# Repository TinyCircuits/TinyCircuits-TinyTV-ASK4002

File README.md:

# TinyCircuits TinyTV
# ASK4002

The design files are located under design_files/ for the TinyTV Remote, other design files can be found under the individual components' name on our GitHub. This Repo contains any files or documentation specific to the TinyTV.

Format is in Cadsoft Eagle format - Eagle version 6.2 was used for the original design.

For more infomation on this, check out the product page at TinyCircuits.com

# License:

Design by TinyCircuits.
All design files are released under the Creative Commons Attribution Share-Alike 3.0 License, see the following link for details: http://creativecommons.org/licenses/by-sa/3.0

All text above must be included in any redistribution or derived design

This project uses designs and concepts developed as part of the Arduino project and the LilyPad project.  The TinyCircuits design files themselves (schematics, PCB and libraries) are not directly derived from these works' design files and have been created new, however the concepts and basic architecture behind the TinyDuino and TinyLily products are derived and we thank the hard work of the organizations below for their contributions to open-source hardware:
  
Original Arduino Uno Design by Team Arduino

LilyPad Arduino Design by Leah Buechley and Sparkfun Electronics

Please support the open-source hardware community

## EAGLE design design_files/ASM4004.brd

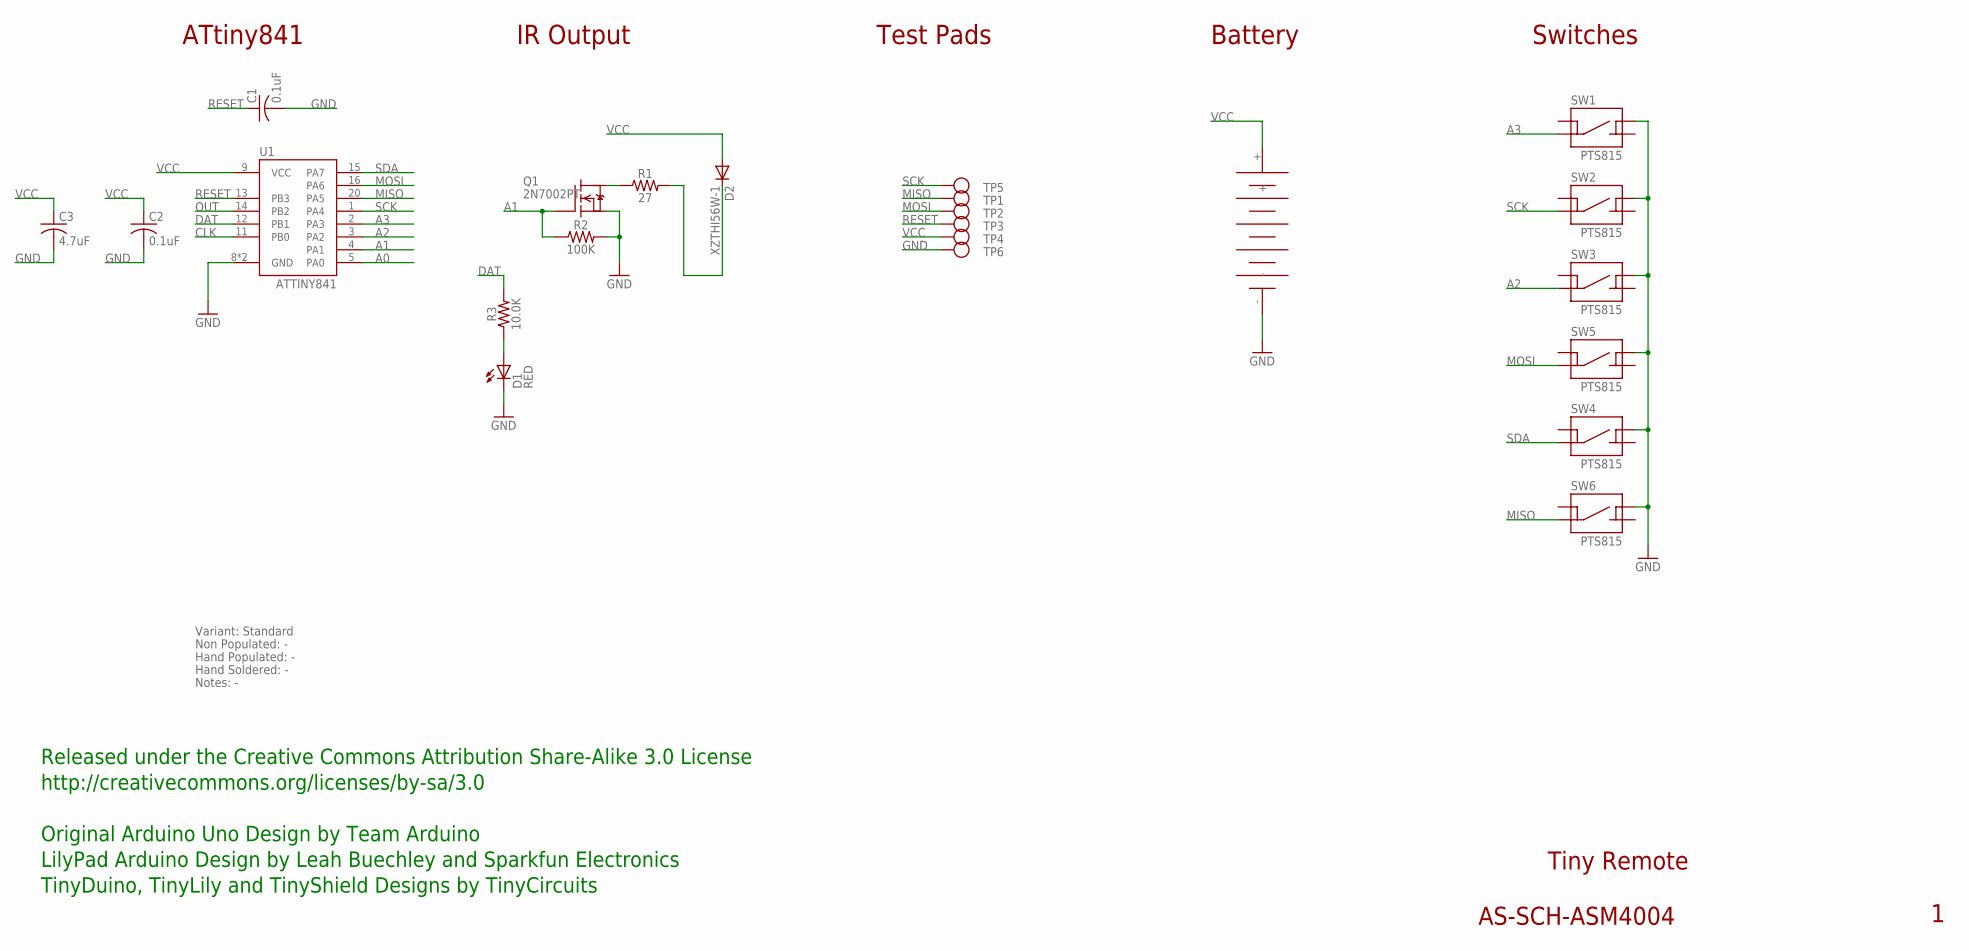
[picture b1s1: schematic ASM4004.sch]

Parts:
C1: 0.1uF; C0402; PARTNO AS-ITM-00008
C2: 0.1uF; C0402
C3: 4.7uF; C0402; PARTNO AS-ITM-00242
D1: RED; 0402_LED; PARTNO AS-ITM-00057
D2: XZTHI56W-1; LED_SIDE_3.0X1.0; PARTNO AS-ITM-00551
J2: 1225; COIN_1220_SMD; PARTNO AS-ITM-00468
Q1: 2N7002PT; SOT-416
R1: 27; 0402; PARTNO AS-ITM-00240
R2: 100K; 0402
R3: 10.0K; 0402; PARTNO AS-ITM-00032
SW1, SW2, SW3, SW4, SW5, SW6: PTS815; PARTNO AS-ITM-00544
TP1, TP2, TP3, TP4, TP5, TP6: TEST_POINT; TEST_POINT_1MM
U1: ATTINY841; VQFN-20

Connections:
A0: U1.5 (PA0)
A1: Q1.1 (G), R2.1, U1.4 (PA1)
A2: SW3.1, U1.3 (PA2)
A3: SW1.1, U1.2 (PA3)
CLK: U1.11 (PB0)
DAT: R3.2, U1.12 (PB1)
GND: C1.2, C2.2, C3.2, D1.2 (C), J2.-, Q1.2 (S), R2.2, SW1.4, SW2.4, SW3.4, SW4.4, SW5.4, SW6.4, TP6.P$1, U1.8 (GND), U1.PAD (GND)
MISO: SW6.1, TP1.P$1, U1.20 (PA5)
MOSI: SW5.1, TP2.P$1, U1.16 (PA6)
unnamed: Q1.3 (D), R1.1
unnamed: D2.C, R1.2
unnamed: D1.1 (A), R3.1
OUT: U1.14 (PB2)
RESET: C1.1, TP3.P$1, U1.13 (PB3)
SCK: SW2.1, TP5.P$1, U1.1 (PA4)
SDA: SW4.1, U1.15 (PA7)
VCC: C2.1, C3.1, D2.A, J2.+, TP4.P$1, U1.9 (VCC)

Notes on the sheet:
Tiny Remote
AS-SCH-ASM4004
Test Pads
ATtiny841
Battery
IR Output
Variant: Standard
Non Populated: -
Hand Populated: -
Hand Soldered: -
Notes: -
Switches
Released under the Creative Commons Attribution Share-Alike 3.0 License
http://creativecommons.org/licenses/by-sa/3.0
Original Arduino Uno Design by Team Arduino
TinyDuino, TinyLily and TinyShield Designs by TinyCircuits
LilyPad Arduino Design by Leah Buechley and Sparkfun Electronics

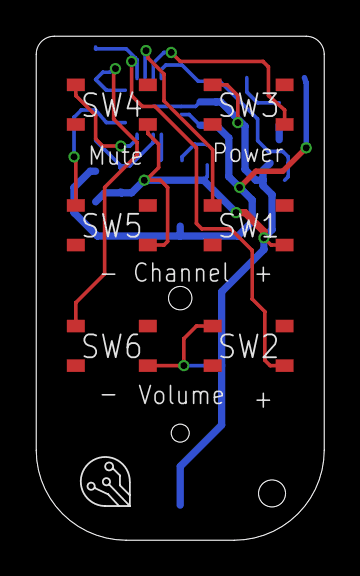
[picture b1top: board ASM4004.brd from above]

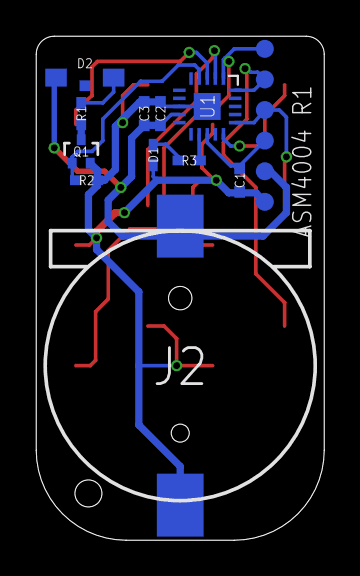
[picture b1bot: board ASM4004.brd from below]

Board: 2 copper layers, 16.0 x 28.0 mm, 24 parts (17 on the bottom side), 14 nets.

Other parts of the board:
U$1: DOCFIELD-TINYCIRCUITS-PCB

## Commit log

2019-12-02 images
2019-12-02 more images
2019-12-04 tv files
2019-12-09 program
2019-12-13 update code comment
2020-05-01 fix speaker image
2020-05-14 Add tiny video player updated code
2020-05-18 new button image
2020-12-24 videos
2021-01-04 New TSV Converter
2021-01-04 make lower left button configurable to "power off" or channel down
2021-01-06 fix chanDwn bug - short circuit eval needed
2021-03-18 update windows converter
2021-12-07 add bootloader image
